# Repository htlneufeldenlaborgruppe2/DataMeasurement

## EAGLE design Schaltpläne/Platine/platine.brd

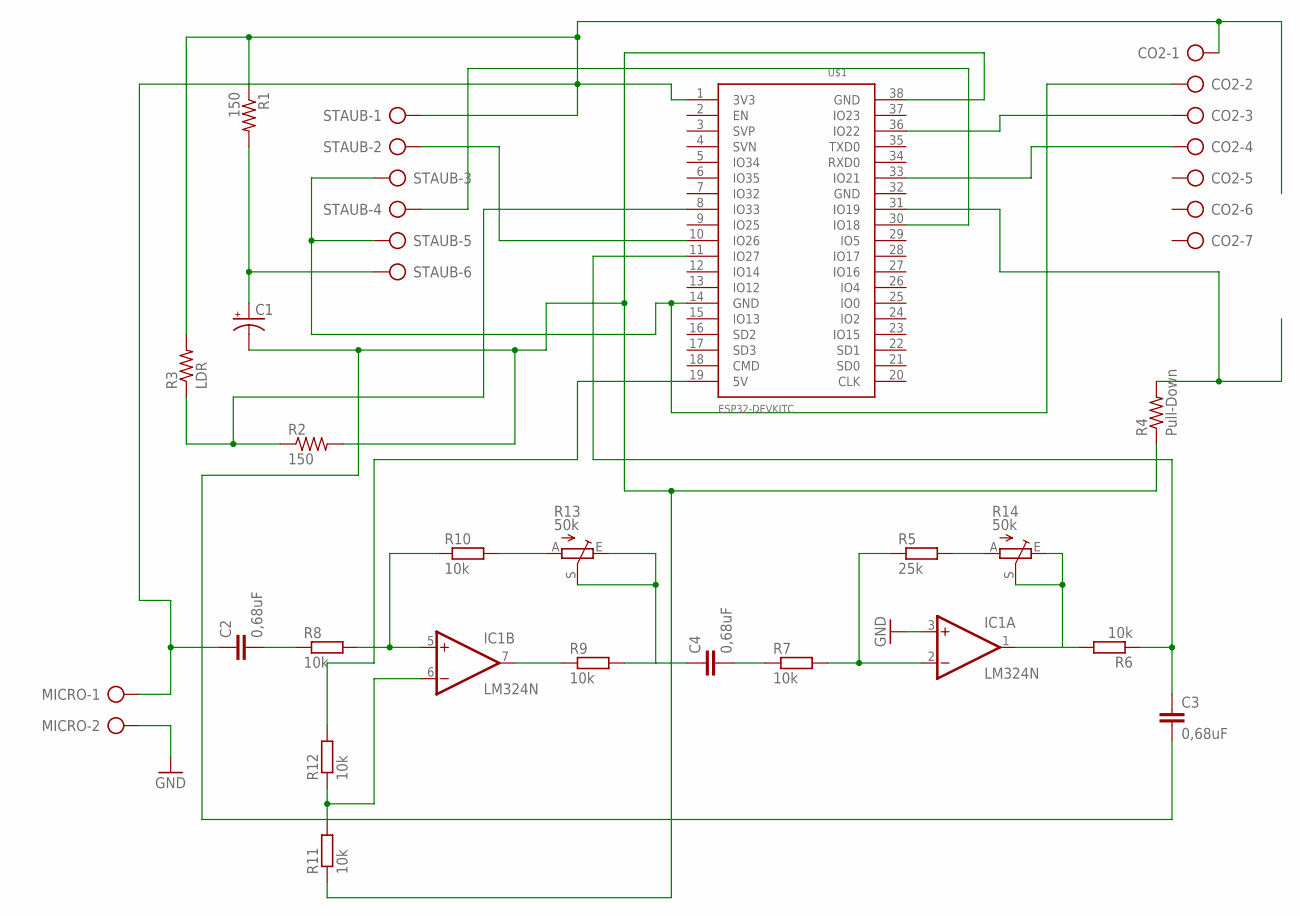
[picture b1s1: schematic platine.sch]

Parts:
C1: CPOL-USE2,5-6E; E2,5-6E
C2, C3, C4: 0,68uF; C025-025X050
CO2: AK300/7
IC1: LM324N; DIL14
MICRO: AK300/2
R1, R2: 150; 0207/10
R3: LDR; V234/12
R4: Pull-Down; 0207/10
R5: 25k; 0204/7
R6, R7, R8, R9, R10, R11, R12: 10k; 0204/7
R13, R14: 50k; LI10
STAUB: AK300/6
U$1: ESP32DEVKITC; ESP32-DEVKITC

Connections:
GND: IC1.3 (+IN), MICRO.2
unnamed: STAUB.2, U$1.10 (IO26)
unnamed: C1.+, R1.2, STAUB.6
unnamed: R12.2, U$1.19 (5V)
unnamed: STAUB.4, U$1.30 (IO18)
unnamed: CO2.3, U$1.36 (IO22)
unnamed: CO2.4, U$1.33 (IO21)
unnamed: R2.1, R3.1, U$1.8 (IO33)
unnamed: R4.2, U$1.31 (IO19)
unnamed: C2.1, CO2.1, MICRO.1, R1.1, R3.2, STAUB.1, U$1.1 (3V3)
unnamed: C3.1, R6.1, U$1.11 (IO27)
unnamed: R10.2, R13.A
unnamed: C4.1, R9.2, R13.E, R13.S
unnamed: IC1.7 (OUT), R9.1
unnamed: IC1.5 (+IN), R8.2, R10.1
unnamed: C2.2, R8.1
unnamed: IC1.6 (-IN), R11.2, R12.1
unnamed: C4.2, R7.1
unnamed: IC1.2 (-IN), R5.1, R7.2
unnamed: IC1.1 (OUT), R6.2, R14.E, R14.S
unnamed: R5.2, R14.A
unnamed: C1.-, C3.2, R2.2, R4.1, R11.1, U$1.38 (GND)
unnamed: CO2.2, STAUB.3, STAUB.5, U$1.14 (GND)
V+: IC1.4 (V+)
V-: IC1.11 (V-)

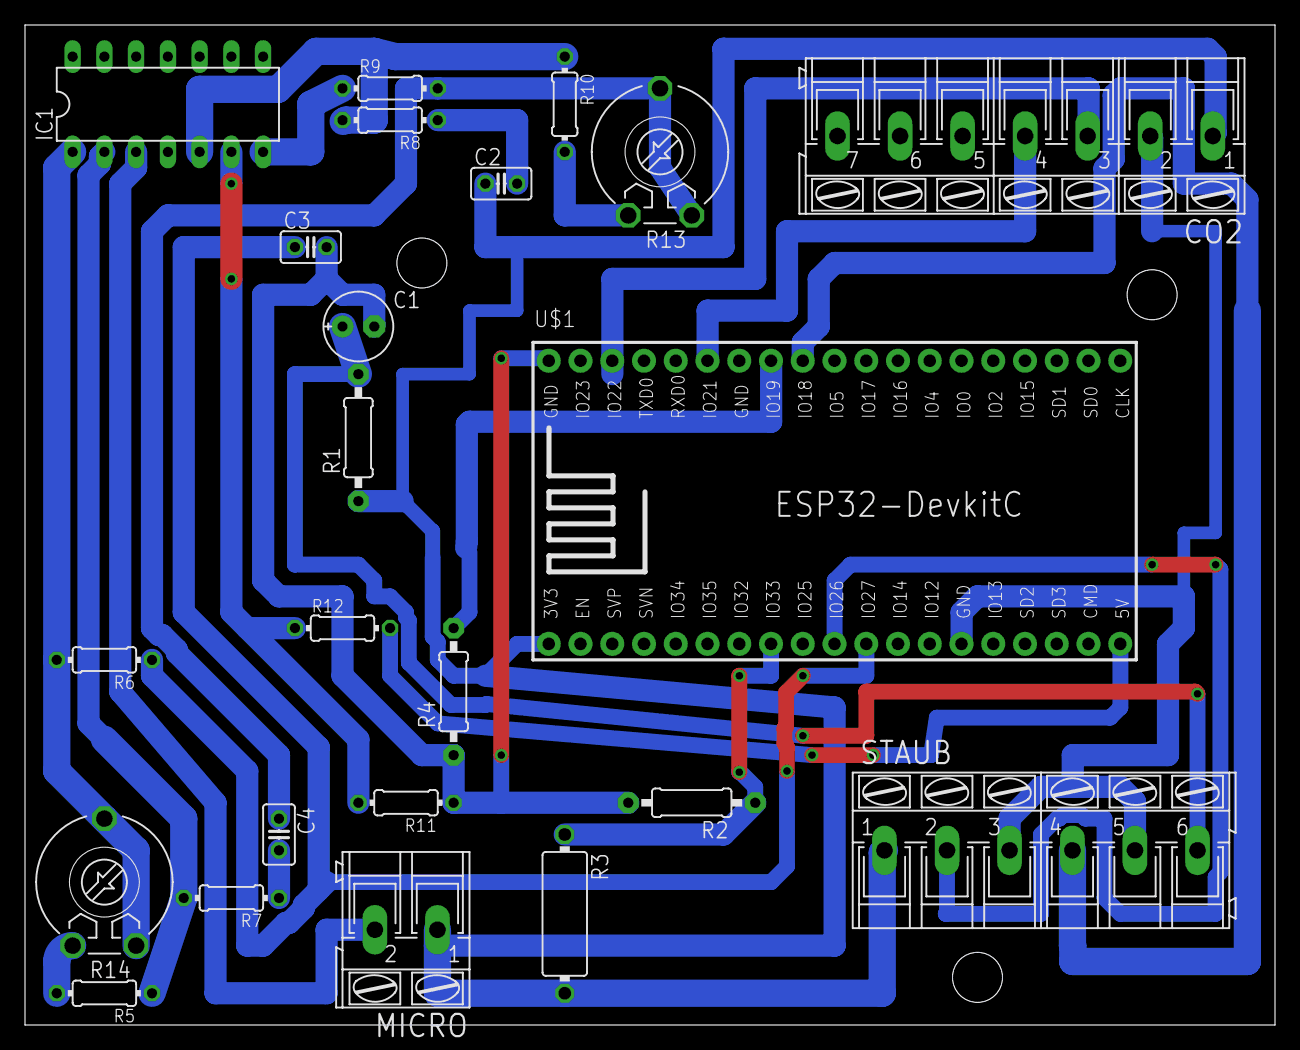
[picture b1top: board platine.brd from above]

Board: 2 copper layers, 100.0 x 80.0 mm, 23 parts (0 on the bottom side), 23 nets.

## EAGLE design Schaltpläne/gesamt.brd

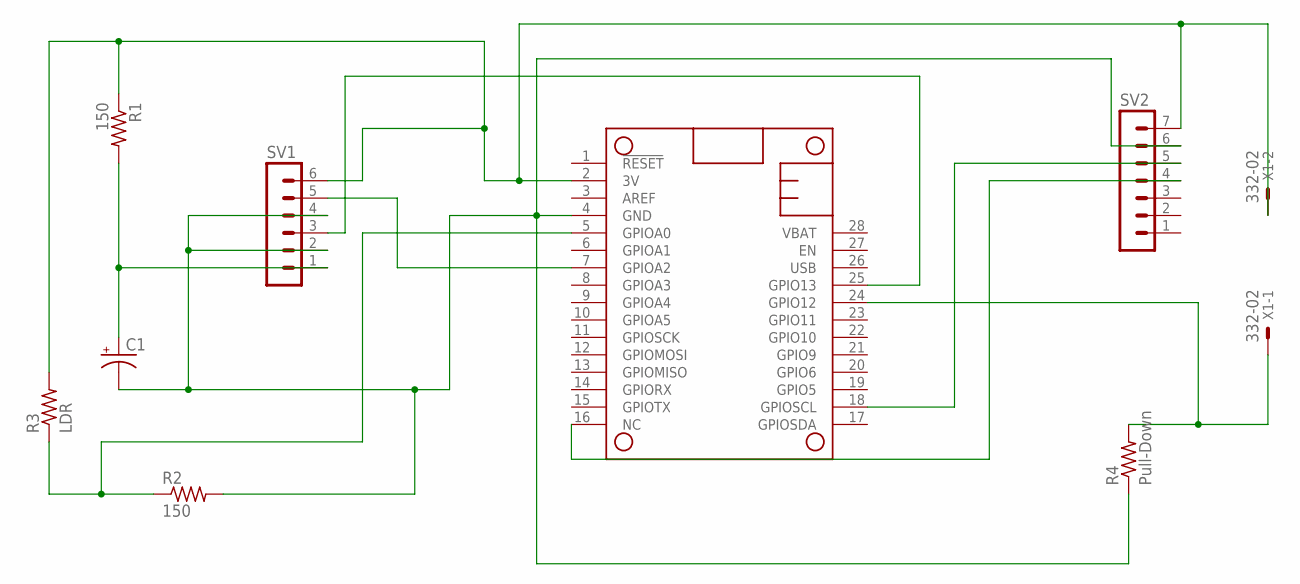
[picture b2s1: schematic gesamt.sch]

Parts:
C1: CPOL-USE2,5-6E; E2,5-6E
MS1: FEATHERWING
R1, R2: 150; 0207/10
R3: LDR; V234/12
R4: Pull-Down; 0207/10
SV1: MA06-1
SV2: MA07-1
X1: 332-02

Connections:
3V: MS1.2 (3V), R1.1, R3.2, SV1.6, SV2.7, X1.2
unnamed: MS1.7 (GPIOA2), SV1.5
unnamed: C1.+, R1.2, SV1.1
unnamed: C1.-, MS1.4 (GND), R2.2, R4.1, SV1.2, SV1.4, SV2.6
unnamed: MS1.25 (GPIO13), SV1.3
unnamed: MS1.18 (GPIOSCL), SV2.5
unnamed: MS1.16 (NC), SV2.4
unnamed: MS1.5 (GPIOA0), R2.1, R3.1
unnamed: MS1.24 (GPIO12), R4.2, X1.1

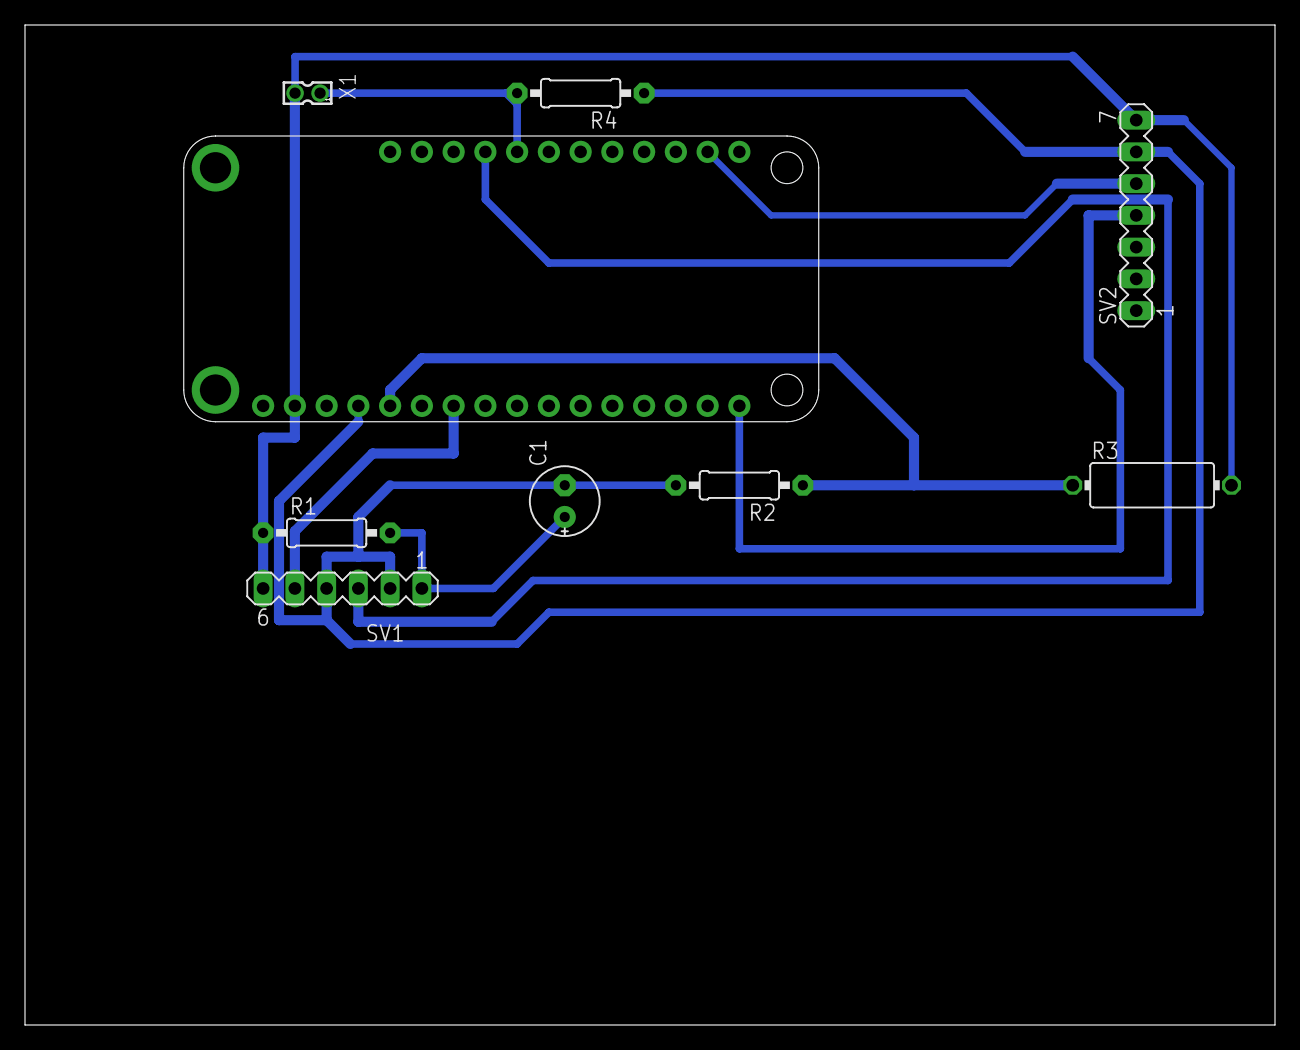
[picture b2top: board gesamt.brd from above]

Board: 2 copper layers, 100.0 x 80.0 mm, 9 parts (0 on the bottom side), 9 nets.

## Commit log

2019-04-12 Set theme jekyll-theme-cayman
2019-05-04 added Schaltpläne
2019-05-04 added gitignore, added RaspReceiver1 c#-project
2019-05-04 Schaltplan updated , LDR, Dust, CO2 and Reed
2019-05-04 updated gesamten Schaltplan
2019-05-05 added WebInterface-Project
2019-05-06 established ef-connection
2019-05-06 ran npm upgrade --all --force, audit fixed. Seems to work
2019-05-06 i lOvE npM.... Finished to include module ChartsModule after just working for about 4 hours. Upgraded nearly all packages to newest version (Find and Replaced 5.2.0 with 7.2.0, afterwards npm audit f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
2019-05-07 asdf
2019-05-07 added loadingAnimation
2019-05-09 reedSensor
2019-05-09 gitignore
2019-05-16 Sensor
2019-05-16 without reed
2019-05-16 oof2
2019-05-16 oof3
2019-05-16 noise
2019-05-16 noisemin/max
2019-05-16 oof4
2019-05-16 changesoof5
2019-05-16 oof6
2019-05-16 oof7
2019-05-16 noisAllValuesoof8
2019-05-17 aktueller Schaltplan
2019-05-17 coffee
2019-05-17 changed RaspSend
2019-05-23 added table-generator
2019-05-24 tablebursch
2019-05-24 mover Rasp to new repos
2019-05-24 tabelle
2019-06-07 changed pins
2019-10-31 Bump lodash
    Bumps [lodash](https://github.com/lodash/lodash) from 4.17.11 to 4.17.15.
    - [Release notes](https://github.com/lodash/lodash/releases)
    - [Commits](https://github.com/lodash/lodash/compare/4.17.11...4.17.15)
2019-11-20 Bump stringstream
    Bumps [stringstream](https://github.com/mhart/StringStream) from 0.0.5 to 0.0.6.
    - [Release notes](https://github.com/mhart/StringStream/releases)
    - [Commits](https://github.com/mhart/StringStream/compare/v0.0.5...v0.0.6)
2019-11-20 Bump lodash.mergewith
    Bumps [lodash.mergewith](https://github.com/lodash/lodash) from 4.6.1 to 4.6.2.
    - [Release notes](https://github.com/lodash/lodash/releases)
    - [Commits](https://github.com/lodash/lodash/commits)
2019-11-20 Bump extend
    Bumps [extend](https://github.com/justmoon/node-extend) from 3.0.1 to 3.0.2.
    - [Release notes](https://github.com/justmoon/node-extend/releases)
    - [Changelog](https://github.com/justmoon/node-extend/blob/master/CHANGELOG.md)
    - [Commits](https://github.com/justmoon/node-extend/compare/v3.0.1...v3.0.2)
2019-11-20 Bump fstream
    Bumps [fstream](https://github.com/npm/fstream) from 1.0.11 to 1.0.12.
    - [Release notes](https://github.com/npm/fstream/releases)
    - [Commits](https://github.com/npm/fstream/compare/v1.0.11...v1.0.12)
2019-11-20 Bump diff
    Bumps [diff](https://github.com/kpdecker/jsdiff) from 3.4.0 to 3.5.0.
    - [Release notes](https://github.com/kpdecker/jsdiff/releases)
    - [Changelog](https://github.com/kpdecker/jsdiff/blob/master/release-notes.md)
    - [Commits](https://github.com/kpdecker/jsdiff/compare/v3.4.0...v3.5.0)
2019-11-20 Bump mixin-deep
    Bumps [mixin-deep](https://github.com/jonschlinkert/mixin-deep) from 1.3.1 to 1.3.2.
    - [Release notes](https://github.com/jonschlinkert/mixin-deep/releases)
    - [Commits](https://github.com/jonschlinkert/mixin-deep/compare/1.3.1...1.3.2)
2019-11-20 Bump tar
    Bumps [tar](https://github.com/npm/node-tar) from 2.2.1 to 2.2.2.
    - [Release notes](https://github.com/npm/node-tar/releases)
    - [Commits](https://github.com/npm/node-tar/compare/v2.2.1...v2.2.2)
2019-11-20 Bump sshpk
    Bumps [sshpk](https://github.com/joyent/node-sshpk) from 1.13.1 to 1.16.1.
    - [Release notes](https://github.com/joyent/node-sshpk/releases)
    - [Commits](https://github.com/joyent/node-sshpk/compare/v1.13.1...v1.16.1)
2019-12-28 Bump handlebars
    Bumps [handlebars](https://github.com/wycats/handlebars.js) from 4.1.2 to 4.5.3.
    - [Release notes](https://github.com/wycats/handlebars.js/releases)
    - [Changelog](https://github.com/wycats/handlebars.js/blob/master/release-notes.md)
    - [Commits](https://github.com/wycats/handlebars.js/compare/v4.1.2...v4.5.3)
2020-03-14 Bump acorn
    Bumps [acorn](https://github.com/acornjs/acorn) from 6.1.1 to 6.4.1.
    - [Release notes](https://github.com/acornjs/acorn/releases)
    - [Commits](https://github.com/acornjs/acorn/compare/6.1.1...6.4.1)
2020-04-16 Bump https-proxy-agent
    Bumps [https-proxy-agent](https://github.com/TooTallNate/node-https-proxy-agent) from 2.2.1 to 2.2.4.
    - [Release notes](https://github.com/TooTallNate/node-https-proxy-agent/releases)
    - [Commits](https://github.com/TooTallNate/node-https-proxy-agent/compare/2.2.1...2.2.4)
2020-06-06 Bump websocket-extensions
    Bumps [websocket-extensions](https://github.com/faye/websocket-extensions-node) from 0.1.3 to 0.1.4.
    - [Release notes](https://github.com/faye/websocket-extensions-node/releases)
    - [Changelog](https://github.com/faye/websocket-extensions-node/blob/master/CHANGELOG.md)
    - [Commits](https://github.com/faye/websocket-extensions-node/compare/0.1.3...0.1.4)
2020-07-17 Bump lodash
    Bumps [lodash](https://github.com/lodash/lodash) from 4.17.15 to 4.17.19.
    - [Release notes](https://github.com/lodash/lodash/releases)
    - [Commits](https://github.com/lodash/lodash/compare/4.17.15...4.17.19)
2020-07-30 Bump elliptic
    Bumps [elliptic](https://github.com/indutny/elliptic) from 6.4.1 to 6.5.3.
    - [Release notes](https://github.com/indutny/elliptic/releases)
    - [Commits](https://github.com/indutny/elliptic/compare/v6.4.1...v6.5.3)
2020-09-04 Bump node-sass
    Bumps [node-sass](https://github.com/sass/node-sass) from 4.9.0 to 4.13.1.
    - [Release notes](https://github.com/sass/node-sass/releases)
    - [Changelog](https://github.com/sass/node-sass/blob/master/CHANGELOG.md)
    - [Commits](https://github.com/sass/node-sass/compare/v4.9.0...v4.13.1)
2020-09-04 Bump handlebars
    Bumps [handlebars](https://github.com/wycats/handlebars.js) from 4.1.2 to 4.7.6.
    - [Release notes](https://github.com/wycats/handlebars.js/releases)
    - [Changelog](https://github.com/handlebars-lang/handlebars.js/blob/master/release-notes.md)
    - [Commits](https://github.com/wycats/handlebars.js/compare/v4.1.2...v4.7.6)
2020-09-08 Bump http-proxy
    Bumps [http-proxy](https://github.com/http-party/node-http-proxy) from 1.17.0 to 1.18.1.
    - [Release notes](https://github.com/http-party/node-http-proxy/releases)
    - [Changelog](https://github.com/http-party/node-http-proxy/blob/master/CHANGELOG.md)
    - [Commits](https://github.com/http-party/node-http-proxy/compare/1.17.0...1.18.1)
